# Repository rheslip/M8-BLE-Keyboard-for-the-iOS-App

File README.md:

**BLE Wireless Keyboard for the M8 iOS App**

When I saw that Dirtywave had released an M8 app on iOS one my first thoughts was to make an M8 like keyboard for it. I have an M8 headless that is almost identical to the real M8 and I wanted to leverage the muscle memory I had developed for that.

Altho it was created for use with the iOS app, with some software modifications it would work on a PC with the M8 Headless as well.

Oct 3/2026 - more or less final version of the code which shows battery levels on the RGB LED

Sept 17/2026 - added hardware design files for PCB and two enclosure variants (AAA battery and LiPo with charging jack) - tested and working OK

Video demo of the final version https://www.youtube.com/watch?v=-Xh-XhrWJC8&t=2s

The prototype worked very well so I have designed a PCB and enclosure which more or less duplicates the M8 V1 design - eight Kailh switches, approx 97mm x 84mm x18mm, white silkscreen. It has a small RGB led for indicating battery status, pads for a switch and pads for a lipo charger module as well.

M8 V1 and V2 images for reference

PCB images:

 You may notice there is no ground fill on the board. This is intentional - a large GND plane near the antenna will mess with the BLE signal. I also wanted a clean front panel with no visible planes/traces/vias.
 
 3D Renders of the enclosure. Note the cutouts for USB-C charging jack and switch on the LiPo version. A version with no USB jack is provided for use with a AAA battery holder. 

Batteries

I use LiPo batteries and small charger modules from AliExpress. The PCB footprint is for this one which has a LiPo protection circuit as well but you can barnacle almost any of these on and make it work.

**CAUTION this TP4056 charger module is set up for 1A charge rate which is too high for most small LiPo's** 
To be safe you will want to change the current setting resistor to something like 1/3 of the battery capacity.

**LiPo batteries are a fire hazard!!! Do not use a LiPo unless you are comfortable modifying the module appropriately, testing it, and are willing to take the risk**

Alternatively use 3 AAA batteries which is much safer. You can use 2x AAA as well but the battery life will be reduced by 1/3.
The battery indicator is set up for the range of a LiPo 4.2V full, 3V cutoff which is about the same voltage range as three AAA. If you use something else you will need to modify the sketch.

Power consumption of the Pico 2 W running this sketch is around 40ma at 5V (0.2 watts). If you use three AAA alkalines (around 3WH) the batteries should last around 15 hours. An 800 Mah LiPo should have about the same battery life.
Unfortunately the Pico 2 BLE stack does not support power management or underclocking which would have been nice to extend the battery life.

Usage

I have not had much luck getting the iOS bluetooth settings to see the M8KB device directly. Adafruit's Bluefruit Connect app sees it and pairs with it no problem. After pairing with Bluefruit Connect, iOS will automatically connect to it every time. This is not the first time I've have trouble with bluetooth devices on iOS. There seem to be some subtle incompatibilies between the Pico's implementation of BLE and what Apple wants to see.

If you recompile and reinstall the firmware you have to forget the device and pair it again on your iPad/iPhone. 

The default key bindings are set up to work with the M8 app default keyboard assignment but you may have to re-bind the key assignments in the M8 app to get everything working correctly. In particular the M8 app sees the SHIFT and EDIT keys as the same key until you re-bind them. I think this is because the Arduino keyboard library treats the shift key as a modifier and not as a separate key. You will only have to do this once - the M8 app remembers the key bindings.

Another oddity is that if you are using the M8 app in AUM when you switch to another AUV3 plugin and come back to M8 it loses the connection to M8KB. You can restore it by double tapping the screen to hide/show the on screen controls. M8KB does not show up in the device list in AUM either but it works OK other than the aforementioned disconnect. More weirdness with Pico + iOS BLE or perhaps a bug in the M8 app. 

It connects to a PC but doesn't work with M8 web display. It would probably work by changing the Pico library from keyboardBLE to gamepadBLE. More testing is needed.

Assembly

Solder the three 0603 resistors, the .1u cap and the schottky diode. Solder in the RGB LED making sure that the orientation matches the silkscreen and make sure the lens is facing the FRONT of the PCB. If you don't want to source this LED, you can barnacle an SMT LED or even a 3mm LED to the pads but you will have to modify the sketch to make it blink or something when the battery is low.

Solder the Pico 2W to the pads. 
If you think you may want to remove it at some point best to use small wires or perhaps put some kapton tape on the bottom of the Pico - if the pads have been soldered directly to the PCB pads its very hard to desolder. Also make sure the USB connector edge is flush with the PCB edge - you don't want it to stick out because there is no provision for it in the enclosure. ie load the firmware with the board out of the enclosure.

Solder in the Kailh 1350 switches so the plungers are on the front side of the PCB (obviously). These switches are the same ones used on the M8 and they are available with different actuation forces and "clickiness". The M8 has removable switches - I had the sockets in the design and then took them out. M8 users probably already know which switches they like.

If you are using a LiPo, solder the charger module to the four pads so the USB jack faces to the left with the board switch side up. Solder the negative battery lead to the B- pad on the charger module. At this point its a very good idea to put a current meter between the B+ pad and the battery + lead - make sure the power switch is off. If everything is OK there should be just a very tiny leakage current. If not, you probably have a bad module. I always check the charging current at this stage as well.

If you are using a AAA holder, solder the +ve lead to the OUT+ pad and the -ve lead to OUT- pad. A 3x AAA battery holder should just fit between the Pico and the charger pads and can be stuck to the PCB with double sided foam tape. 

I couldn't find a suitable PCB mounted R/A slide switch so I went with PCB pads so you can solder in whatever you have. I use small slide switches about 5mm thick by 13mm wide. Glue it to the PCB and wire the switch leads to the provided pads. Make sure the switch is flush with the edge of the PCB and aligned with the switch cutout in the enclosure.

The mounting holes in the enclosure are sized for 4-40 or 3mm screws - tap the holes. You could also use small wood or plastic cutting screws.

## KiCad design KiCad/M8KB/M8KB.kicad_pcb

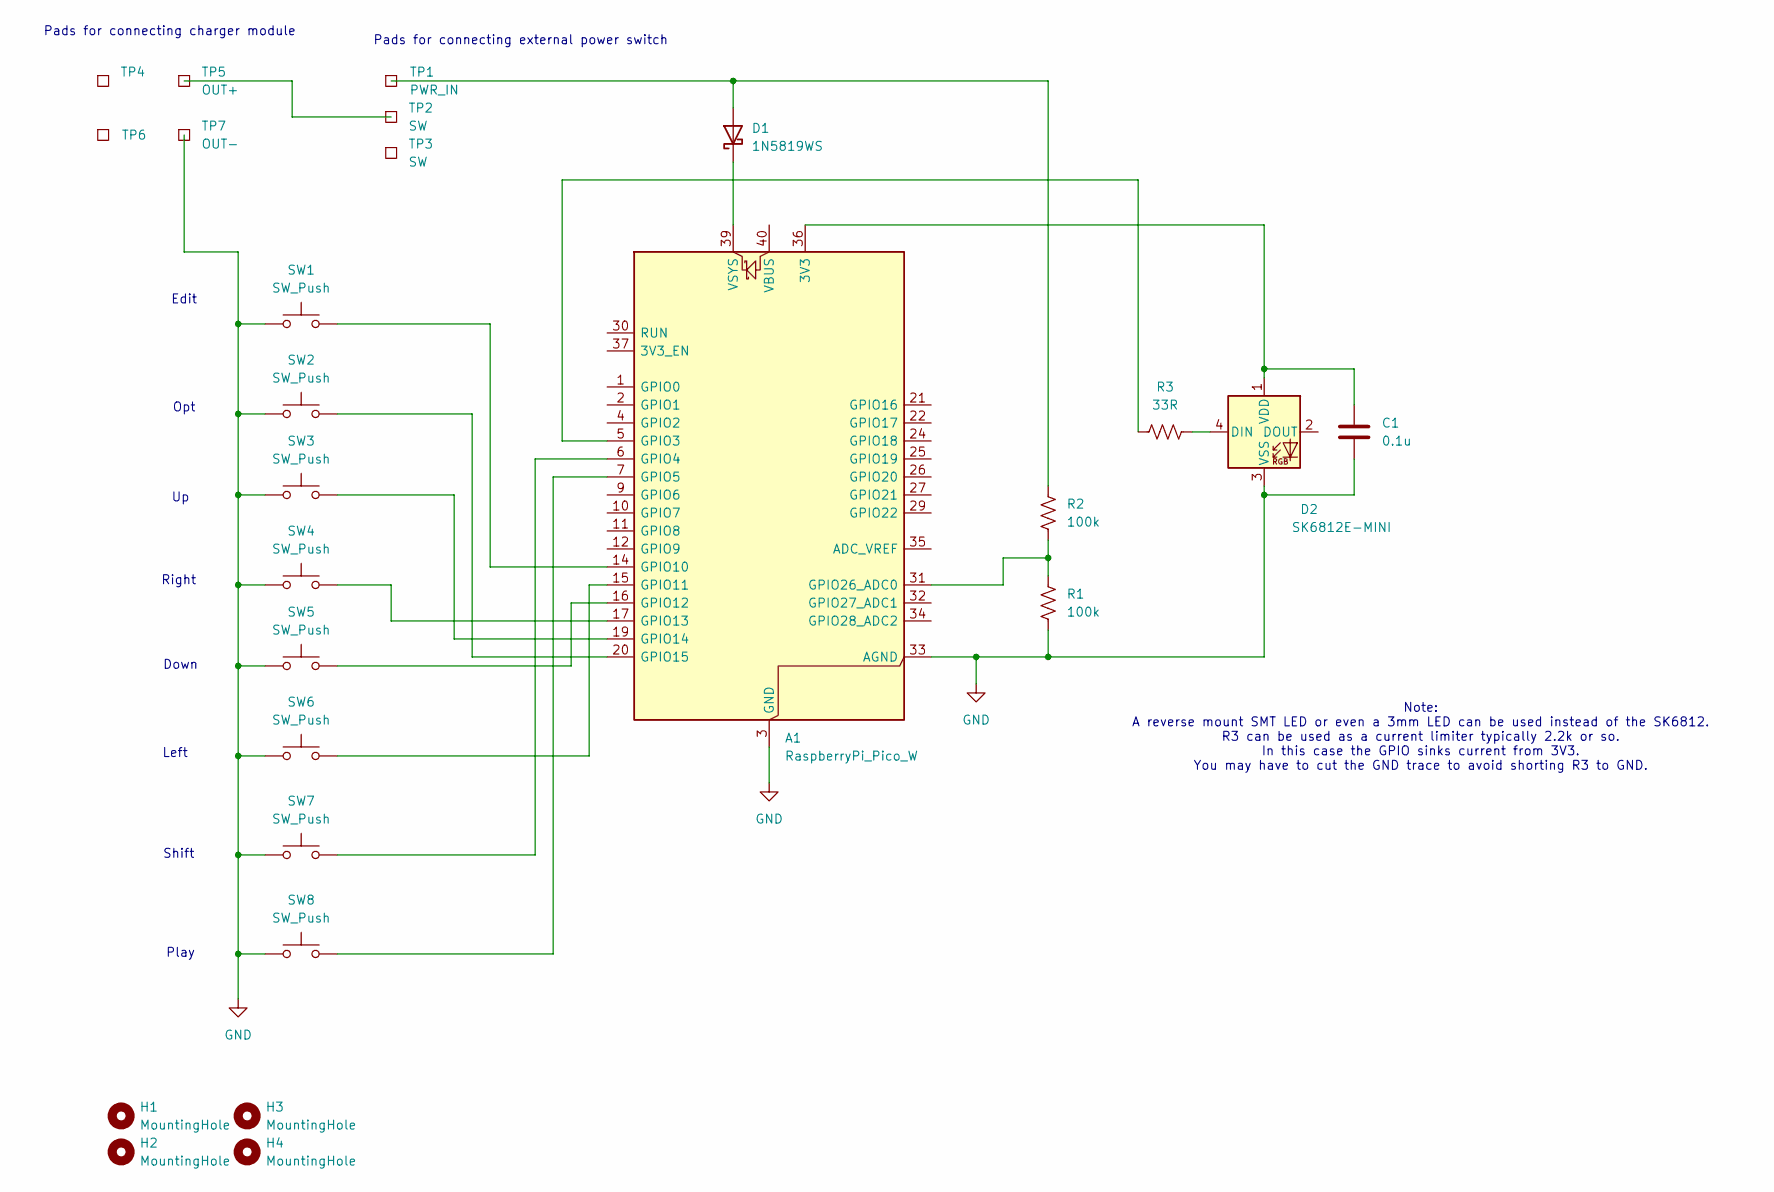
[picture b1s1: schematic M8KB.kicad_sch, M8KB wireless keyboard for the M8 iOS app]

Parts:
A1: RaspberryPi_Pico_W; RaspberryPi_Pico_SMD
C1: 0.1u; C_0603_1608Metric_Pad1.08x0.95mm_HandSolder
D1: 1N5819WS; D_SOD-323
D2: SK6812E-MINI; LED_OPSCO_SK6812_MINI-E_5.0x5.0mm_P3.1mm_rearmount
H1, H2, H3, H4: MountingHole; MountingHole_3.2mm_M3_ISO14580
R1, R2: 100k; R_0603_1608Metric_Pad0.98x0.95mm_HandSolder
R3: 33R; R_0603_1608Metric_Pad0.98x0.95mm_HandSolder
SW1, SW2, SW3, SW4, SW5, SW6, SW7, SW8: SW_Push; SW_PG1350
TP1: PWR_IN; TestPoint_Pad_2.5x2.5mm
TP2, TP3: SW; TestPoint_Pad_2.5x2.5mm
TP4, TP6: TestPoint_Pad_2.5x2.5mm
TP5: OUT+; TestPoint_Pad_2.5x2.5mm
TP7: OUT-; TestPoint_Pad_2.5x2.5mm

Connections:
GND: A1.3 (GND), A1.8 (GND), A1.13 (GND), A1.18 (GND), A1.23 (GND), A1.28 (GND), A1.33 (AGND), A1.38 (GND), C1.2, D2.3 (VSS), R1.2, SW1.1, SW2.1, SW3.1, SW4.1, SW5.1, SW6.1, SW7.1, SW8.1, TP7.1 (1_1)
unnamed: A1.36 (3V3), C1.1, D2.1 (VDD)
unnamed: A1.5 (GPIO3), R3.1
unnamed: A1.6 (GPIO4), SW7.2
unnamed: A1.7 (GPIO5), SW8.2
unnamed: A1.14 (GPIO10), SW1.2
unnamed: A1.15 (GPIO11), SW6.2
unnamed: A1.16 (GPIO12), SW5.2
unnamed: A1.17 (GPIO13), SW4.2
unnamed: A1.19 (GPIO14), SW3.2
unnamed: A1.20 (GPIO15), SW2.2
unnamed: A1.31 (GPIO26_ADC0), R1.1, R2.2
unnamed: A1.39 (VSYS), D1.1 (K)
unnamed: D1.2 (A), R2.1, TP1.1 (1_1)
unnamed: D2.4 (DIN), R3.2
unnamed: TP2.1 (1_1), TP5.1 (1_1)

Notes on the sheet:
Play
Shift
Left
Note: A reverse mount SMT LED or even a 3mm LED can be used instead of the SK6812. R3 can be used as a current limiter typically 2.2k or so. In this case the GPIO sinks current from 3V3. You may have to cut the GND trace to avoid shorting R3 to GND.
Down
Edit
Pads for connecting charger module
Pads for connecting external power switch
Right
Opt

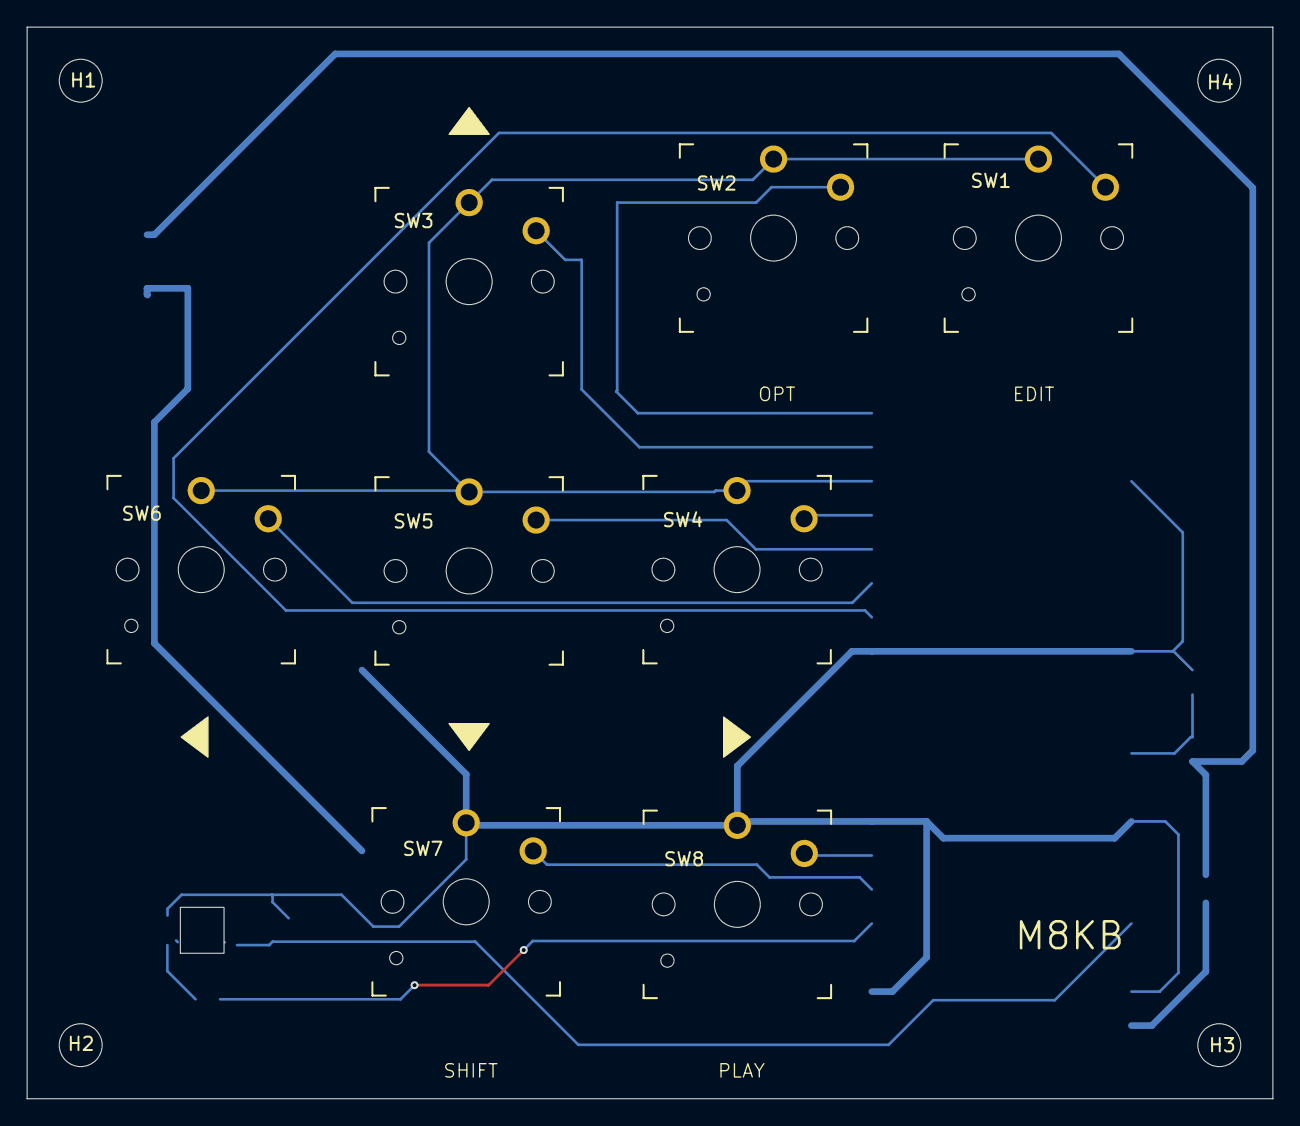
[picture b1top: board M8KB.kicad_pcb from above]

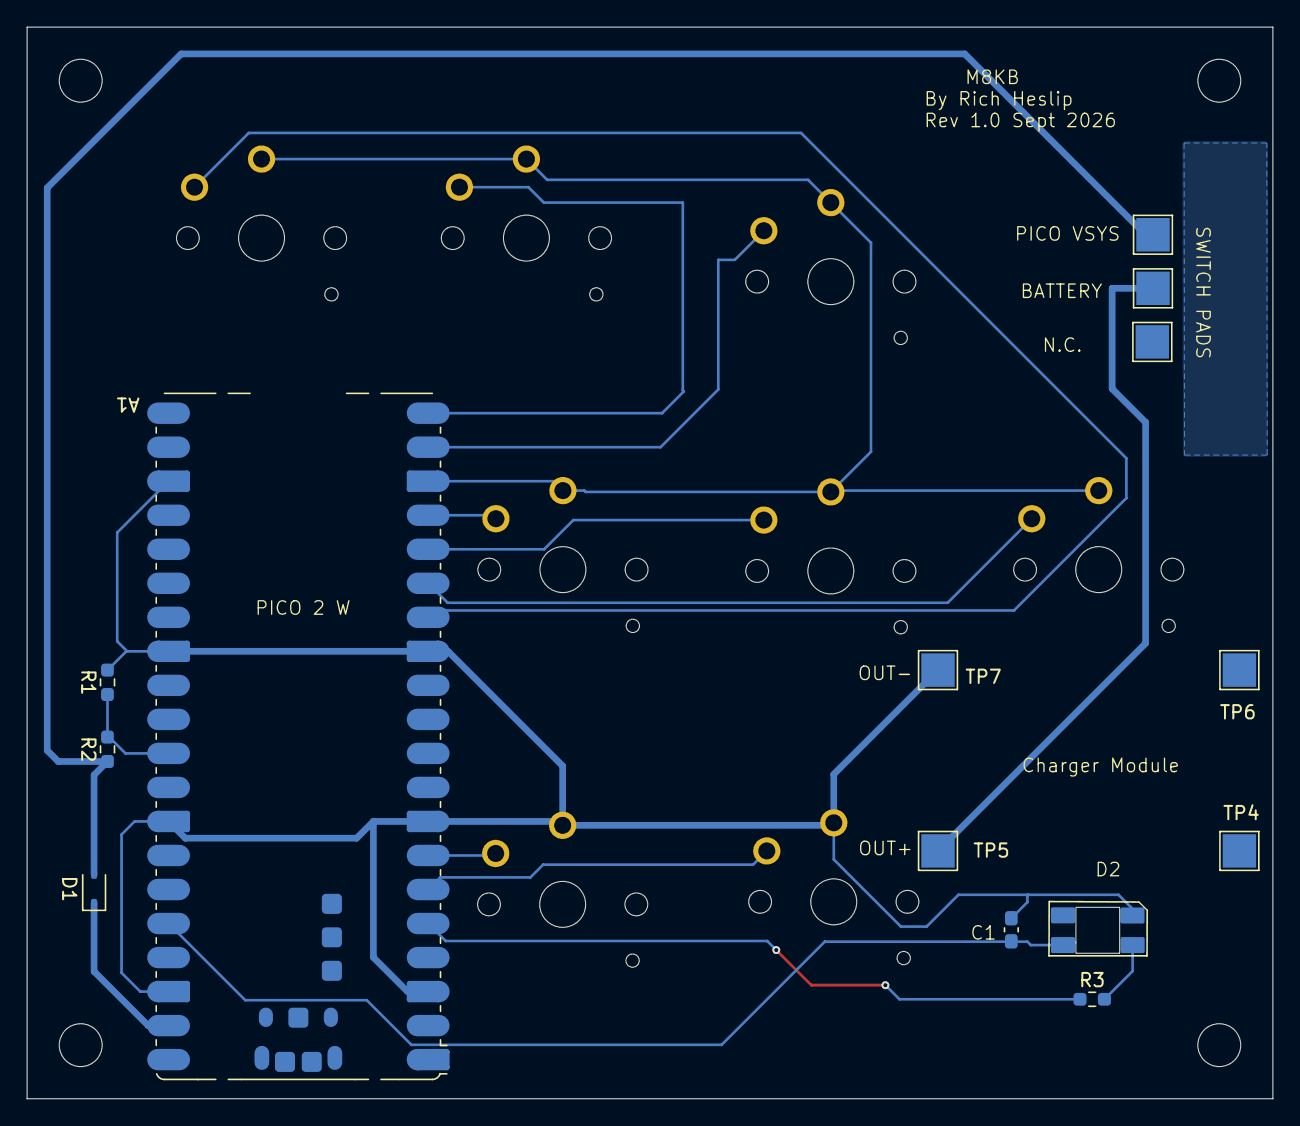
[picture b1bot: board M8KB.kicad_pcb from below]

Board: 2 copper layers, 93.0 x 80.0 mm, 26 parts (14 on the bottom side), 16 nets.
